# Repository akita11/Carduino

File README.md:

# Carduino

Carduino (v4.1)は、クレジットカードサイズ・厚さ2.4mmの、ArduinoUNO互換機です。
財布などにいつもいれておいて、いつでもその場でArduinoを使うことができます。
「Arduinoは興味あるんだけど、まだ触ったことないんだよね」という人に会ったら、その場でArduinoを体験してもらいましょう。
* ArduinoIDEの導入からLチカまでの手順は、本体裏面にシルクで書かれています。またArduinoIDEのダウンロード先もQRコードで読み取れます。
* USB-Aコネクタ（収納式）で、PCのUSB端子に直接差し込むことができます。またUSB Type-Cケーブルで接続することもできます。
* Arduinoの入出力端子はメスソケットですので、ジャンパワイヤ等をさしてつかうこともできます。
* USB-シリアル変換には、FTDI FT232Rを使っています。
* [スイッチサイエンスで委託販売はじまりました](https://www.switch-science.com/catalog/6368/)

# 使い方

本体裏面のシルクを参照してください。

PCとの接続は、以下の2通りが可能です。
* 本体のコネクタをいったんはずし、以下のようにとりつけ、PCのUSBポートに直接さしこみます。（※コネクタの向きに注意してください。収納時とは表裏を逆にさして使用します。表裏を逆で使用すると、本体やPCを破損する恐れがあります）

* USB Type-Cケーブルを本体コネクタ部にさしこみます。

なお未使用時にUSBコネクタ部を格納しておくコネクタには、A6/A7、電源5V、GNDがつながっています。

# 作り方

* ガーバーデータ(Carduino_v41_gerber.zip)で基板製造（板厚0.6mm）し、部品表（Carduino_v41_bom.xlsx）の部品をとりつけます。
* 4p、6p、8pのピンソケット（各2個：秋月電子等で購入できます）を、基板の溝にあわせて横向けにはんだ付けします。また4pピンヘッダ（秋月電子等で購入できます）をUSBコネクタ側にとりつけます。
* 板厚1mmまたは1.5mmのアクリル板をCarduino_v41_cover.pdfでレーザーカッター等でカットし、本体に透明両面テープや透明ボンド等で固定します。
* ArduinoUNO用のブートローダを書き込みます

# 作者

Junichi Akita (akita@ifdl.jp, @akita11)

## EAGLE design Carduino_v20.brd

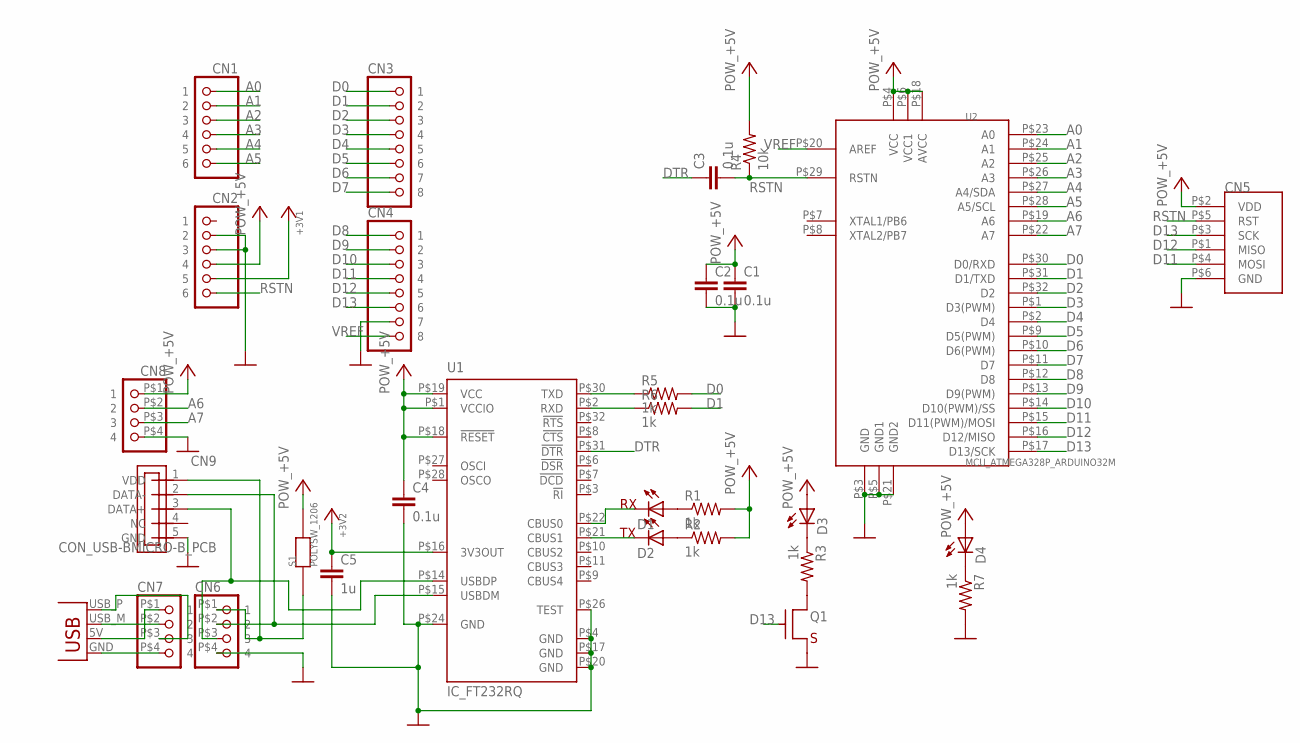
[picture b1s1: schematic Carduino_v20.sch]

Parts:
C1, C2, C3, C4: 0.1u; 0603
C5: 1u; 0603
CN1, CN2: CON_PINHD-1X6SMD; 1X06SMD
CN3, CN4: CON_PINHD-1X8SMD; 1X08SMD
CN5: CON_AVRISPSMD; 2X3SMD
CN6, CN7, CN8: CON_PINHD-1X4SMD; 1X04SMD
CN9: CON_USB-BMICRO-B_PCB; USB-MICRO-PCB
D1, D2, D3, D4: LED0603; SPARKFUN_LED-0603
JP2: CON_USBPCB; USB-A-PCB
Q1: TR_NMOS_IRLML6344; SOT-23-3-2916
R1, R2, R3, R5, R6, R7: 1k; 0603
R4: 10k; 0603
S1: POLYSW_1206; 1206
U1: IC_FT232RQ; QFN32
U2: MCU_ATMEGA328P_ARDUINO32M; QFN32

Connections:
+3V3: C5.1, CN2.P$5 (5), U1.P$16 (3V3OUT)
+5V: C1.1, C2.1, C4.1, CN2.P$4 (4), CN5.P$2 (VDD), CN8.P$1 (1), D3.A, D4.A, R1.2, R2.2, R4.2, S1.P$2, U1.P$1 (VCCIO), U1.P$18 (!RESET), U1.P$19 (VCC), U2.P$4 (VCC), U2.P$6 (VCC1), U2.P$18 (AVCC)
A0: CN1.P$1 (1), U2.P$23 (A0)
A1: CN1.P$2 (2), U2.P$24 (A1)
A2: CN1.P$3 (3), U2.P$25 (A2)
A3: CN1.P$4 (4), U2.P$26 (A3)
A4: CN1.P$5 (5), U2.P$27 (A4/SDA)
A5: CN1.P$6 (6), U2.P$28 (A5/SCL)
A6: CN8.P$2 (2), U2.P$19 (A6)
A7: CN8.P$3 (3), U2.P$22 (A7)
D0: CN3.P$1 (1), R5.2, U2.P$30 (D0/RXD)
D1: CN3.P$2 (2), R6.2, U2.P$31 (D1/TXD)
D2: CN3.P$3 (3), U2.P$32 (D2)
D3: CN3.P$4 (4), U2.P$1 (D3(PWM))
D4: CN3.P$5 (5), U2.P$2 (D4)
D5: CN3.P$6 (6), U2.P$9 (D5(PWM))
D6: CN3.P$7 (7), U2.P$10 (D6(PWM))
D7: CN3.P$8 (8), U2.P$11 (D7)
D8: CN4.P$1 (1), U2.P$12 (D8)
D9: CN4.P$2 (2), U2.P$13 (D9(PWM))
D10: CN4.P$3 (3), U2.P$14 (D10(PWM)/SS)
D11: CN4.P$4 (4), CN5.P$4 (MOSI), U2.P$15 (D11(PWM)/MOSI)
D12: CN4.P$5 (5), CN5.P$1 (MISO), U2.P$16 (D12/MISO)
D13: CN4.P$6 (6), CN5.P$3 (SCK), Q1.1 (G), U2.P$17 (D13/SCK)
DTR: C3.1, U1.P$31 (!DTR)
GND: C1.2, C2.2, C4.2, C5.2, CN2.P$2 (2), CN2.P$3 (3), CN4.P$7 (7), CN5.P$6 (GND), CN6.P$4 (4), CN8.P$4 (4), CN9.5 (GND), Q1.2 (S), R7.2, U1.P$4 (GND), U1.P$17 (GND), U1.P$20 (GND), U1.P$24 (GND), U1.P$26 (TEST), U2.P$3 (GND), U2.P$5 (GND1), U2.P$21 (GND2)
unnamed: D1.A, R1.1
unnamed: D2.A, R2.1
unnamed: R5.1, U1.P$30 (TXD)
unnamed: R6.1, U1.P$2 (RXD)
unnamed: D1.C, U1.P$22 (CBUS0)
unnamed: D2.C, U1.P$21 (CBUS1)
unnamed: D3.C, R3.1
unnamed: CN6.P$2 (2), CN9.2 (DATA-), U1.P$15 (USBDM)
unnamed: CN7.P$4 (4), JP2.GND
unnamed: Q1.3 (D), R3.2
unnamed: CN7.P$1 (1), JP2.5V (VBUS)
unnamed: CN7.P$2 (2), JP2.USB_M (D-)
unnamed: CN7.P$3 (3), JP2.USB_P (D+)
unnamed: D4.C, R7.1
unnamed: CN6.P$3 (3), CN9.3 (DATA+), U1.P$14 (USBDP)
unnamed: CN6.P$1 (1), CN9.1 (VDD), S1.P$1
RSTN: C3.2, CN2.P$6 (6), CN5.P$5 (RST), R4.1, U2.P$29 (RSTN)
VREF: CN4.P$8 (8), U2.P$20 (AREF)

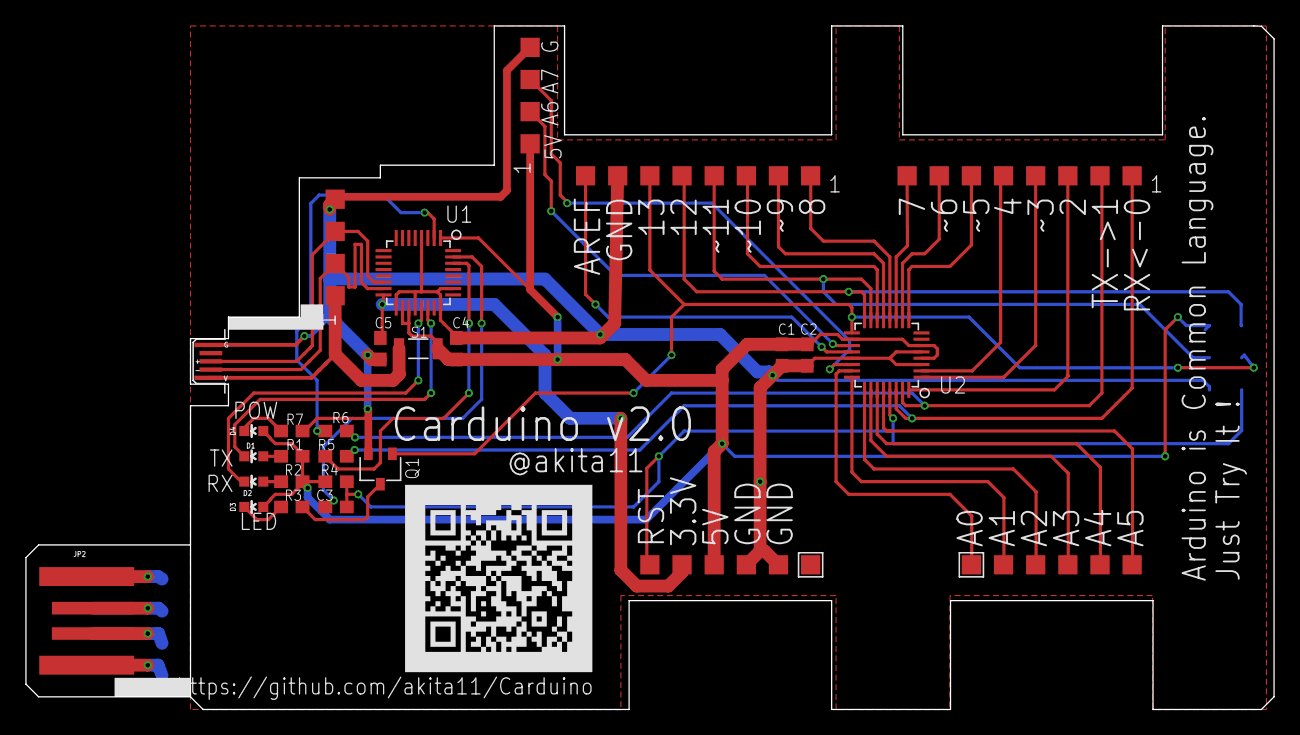
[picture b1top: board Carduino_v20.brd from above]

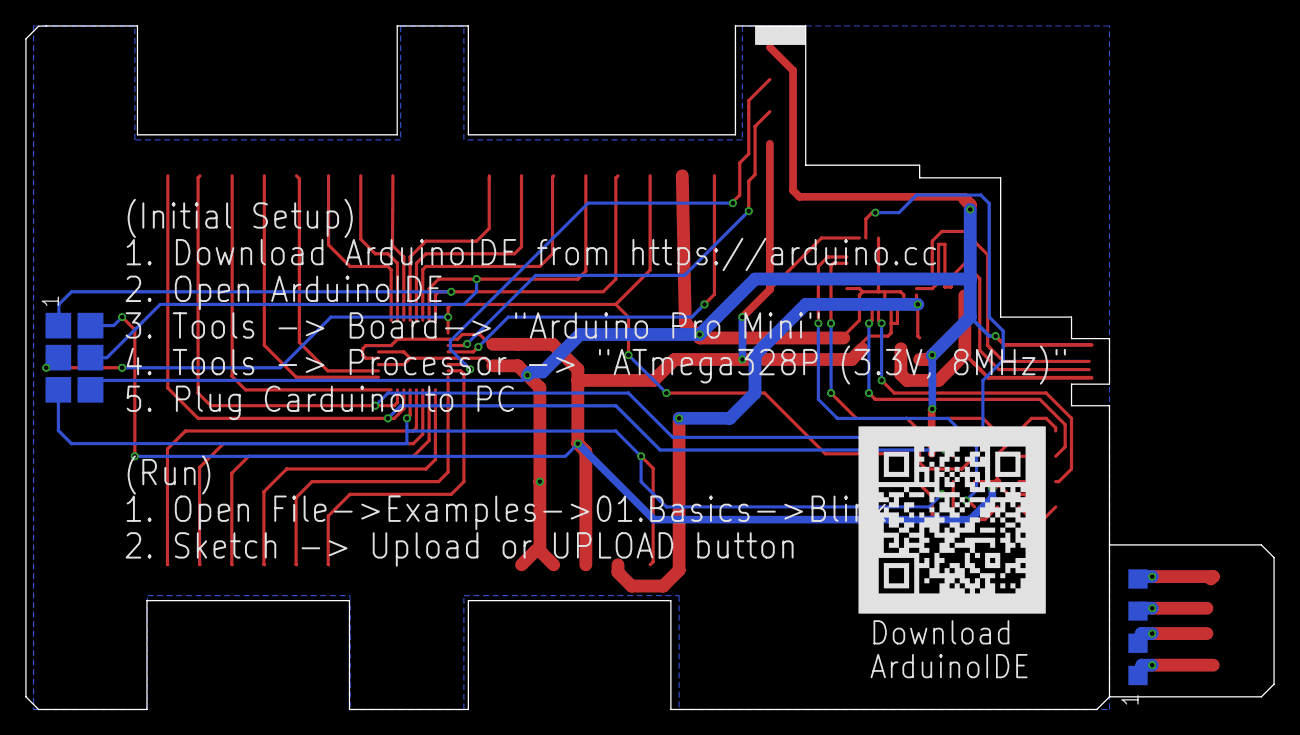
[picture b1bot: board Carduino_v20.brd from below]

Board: 2 copper layers, 98.6 x 54.0 mm, 30 parts (2 on the bottom side), 44 nets.

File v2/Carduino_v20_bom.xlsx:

BOM for Carduino_v11
Elecrow PN | Parts | Value | Package | QTY | Digikey/Mouser/Manufacturer Part | Remark/ Link
2013010A | C1,C3,C4 | 0.1u | C0603 | 3
2013501A | C2,C5 | 1u | C0603 | 2
4040506A | D1 | Red | D0603 | 1
4040706A | D2,D4 | Green | D0603 | 2
4040606A | D3 | Yellow | D0603 | 1
4021523A | Q1 | CJ2302 | SOT23-3 | 1
1022501A | R1,R2,R3,R5,R6,R7 | 1k | R0603 | 6
1023510A | R4 | 10k | R0603 | 1
4060505A | S1 | PolySW | P1206 | 1
 | U1 | FT232RQ |  | 1 | 68-1008-1-ND | FTDI FT232R, QFN32
 | U2 | ATMEGA328P-MU |  | 1 | ATMEGA328P-MUCT-ND | Microchip ATmega328P, QFN32

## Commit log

2018-06-29 readme.mdを修正
2018-06-29 readme.mdを整理
2018-06-29 readme.mdに画像を追加
2018-06-29 コネクタ部の写真のサイズを縮小
2018-06-29 readme.mdを整形
2018-07-01 readme.mdにA6/A7の情報を追記
2018-07-22 readme.mdに委託販売の情報を追記
2020-05-10 v41データの追加
2020-05-11 写真サイズの修正
2020-05-11 コネクタの表裏についての注意を追記
